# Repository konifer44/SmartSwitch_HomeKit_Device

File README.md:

# SmartSwitch compatible with Apple HomeKit Protocol

<br/>

# Project overview

The remotely operated SmartSwitch is designed to turn electrical devices or circuits on and off. The compact size of the device allows for the product to be installed in the housings of other devices. Thanks to its miniature size it fits most of the flush-mounted junction boxes and light switch sockets. The devices can be controlled either via the Apple HomeKit or with buttons connected directly to them.
Using Apple Home app enables automations, scenes and integration with Siri.

<br/>

# Electrical schematic
I have started with an electrical schematic of my device. The basic connections are as specified by the chip manufacturer in [ESP32-WROOM-32d-Datasheet] and the rest depends on my knowledge, experience, and prototyping. 
After creating a schematic I connected all elements on a breadboard. When the breadboard prototype worked successfully I attempted to make PCB.

## Hardware files (v4.0)

- [Eagle schematic (.sch)](hardware/v4.0/smart%20switch.sch)
- [Eagle PCB layout (.brd)](hardware/v4.0/smart%20switch.brd)

## Parts list

| Reference | Qty | Model / value | Function |
| --- | --- | --- | --- |
| U3 | 1 | ESP-WROOM-32 | Wi-Fi and HomeKit controller. |
| HLK1 | 1 | HLK-PM03, 3.3 V (README); HLK-PM01 library device in Eagle | AC-to-DC supply feeding the ESP32 3V3 rail. |
| U2 | 1 | SN74LVC2G17DBV (schematic) | Schmitt-trigger buffer for the physical-switch input to GPIO13. |
| K2 | 1 | OJE-SS-103HM,000 | Normally open load-switching relay. |
| Q1 | 1 | BC849 family, SOT-23 | Relay-coil driver controlled by GPIO27. |
| D1 (formerly R3) | 1 | Diode; model not specified | Coil flyback protection: cathode to VCC, anode to Q1 collector. |
| R1 | 1 | 10 kΩ, 1206 | Physical-switch input pull-down; forms an RC network with C5/C6. |
| R2 | 1 | 10 kΩ, 1206 | ESP32 EN pull-up; forms the reset RC network with C3. |
| R4 | 1 | 4.7 kΩ, 1206 | Q1 base-current limiting. |
| R5 | 1 | 10 kΩ, 1206 | Q1 base-to-emitter pull-down. |
| C1, C2 | 2 | Not specified, 1206 | Supply filtering between VCC and GND. |
| C3 | 1 | Not specified, 1206 | EN-to-GND capacitor in the reset RC network. |
| C4 | 1 | Not specified, polarized, E2-5 footprint | Supply reservoir capacitor between VCC and GND. |
| C5, C6 | 2 | Not specified; C5: C025-024X044, C6: 1206 | Parallel capacitors from switch input to VCC; input filtering with R1. |
| JP1 | 1 | 1×4 header | Programming: GND, RXD0, TXD0, VCC (3.3 V). |
| JP2 | 1 | 1×2 header | GPIO0-to-GND boot-mode jumper. |
| X1 | 1 | AK500/5 terminal block | AC supply, relay contacts, and physical-switch connections. |

The capacitors provide basic power-supply and input filtering, with C3 forming the ESP32 enable/reset RC network. For typical ESP32 supply-decoupling and EN/reset capacitor values, refer to Espressif’s basic ESP32 reference schematics.

<br/>

# PCB designing
The PCB design is based on my electrical schematic. The first step was creating a homemade PCB prototype. When the whole device was mounted, flashed, tested, and running finely I've ordered PCB from [ALLPCB] 

<br/>

## PCB design

<br/>

## Ordered PCB

<br/>

## Prototype & manufactured PCB

<br/><br/>

# Assembly
I have all needed tools and skills to build and flash my device at home .

<br/>

# Writing program 
When I started this project HomeKit Accessory Development Kit (ADK) was available only for MFi Program, also ESP32 manufacture didn't provide any information on how to establish HomeKit connection. I decided to use and modify code from: 
[maximkulkin/esp-homekit]

The whole communication is based on HomeKit Accessory Server from Maxim, but how physically device is working is all my job.
Because Apple doesn't allow to use Apple's WAC (Wireless Accessory Configuration) feature for devices without MFi license we need to provide WiFi credentials in another way.
In Maxim's project the WiFi Credentials are hardcoded and cannot be modified after flashing the device. I have added support for [ESP-IDF Wi-Fi Provisioning], now user can provide WiFi credentials via [ESP SoftAP Provisioning] app even after flashing accessory. The next feature I have added is support for two ways of controlling the accessory. First directly from HomeKit app and the second one by the current wall-mounted physical switch.

## Flashing

<br/>

# Final Mounting

>
* The device is designed to control other electrical devices and
operate in their housings. Faulty connection or use may result in fire or electric shock.

* All works on the device may be performed only by a qualified and licensed electrician. Observe national regulations.

* Even when the device is turned off, voltage may be present at
its terminals. Any maintenance introducing changes into the configuration of connections or the load must be always performed with the disabled fuse or power supply.

<br/>

<br/>

## Provisioning WiFi credentials & adding to HomeKit
As I mentioned before Apple doesn't allow to use Apple's WAC (Wireless Accessory Configuration) feature for devices without MFi license so we will use an official application which is available in AppStore: [ESP SoftAP Provisioning] from [ESP32] manufacturer. After successfully connecting to WiFi the HomeKit Accessory is ready to add to your home.

<br/><br/>

[ESP32]: <https://www.espressif.com/en/products/socs/esp32>
[ESP-IDF]: <https://docs.espressif.com/projects/esp-idf/en/latest/esp32/>
[ESP-IDF Wi-Fi Provisioning]: <https://docs.espressif.com/projects/esp-idf/en/latest/esp32/api-reference/provisioning/wifi_provisioning.html#>

[ESP SoftAP Provisioning]: <https://apps.apple.com/us/app/esp-softap-provisioning/id1474040630>
[LEDC documentation]: <https://docs.espressif.com/projects/esp-idf/en/latest/esp32/api-reference/peripherals/ledc.html>
[Bluetooth Example Walkthrough]: <https://github.com/espressif/esp-idf/blob/1067b28707e527f177752741e3aa08b5dc64a4d7/examples/bluetooth/bluedroid/ble/gatt_server_service_table/tutorial/Gatt_Server_Service_Table_Example_Walkthrough.md>

[ALLPCB]: <https://www.allpcb.com>
[maximkulkin/esp-homekit]: <https://github.com/maximkulkin/esp-homekit>
[ESP32-WROOM-32d-Datasheet]: <https://www.espressif.com/sites/default/files/documentation/esp32-wroom-32d_esp32-wroom-32u_datasheet_en.pdf>

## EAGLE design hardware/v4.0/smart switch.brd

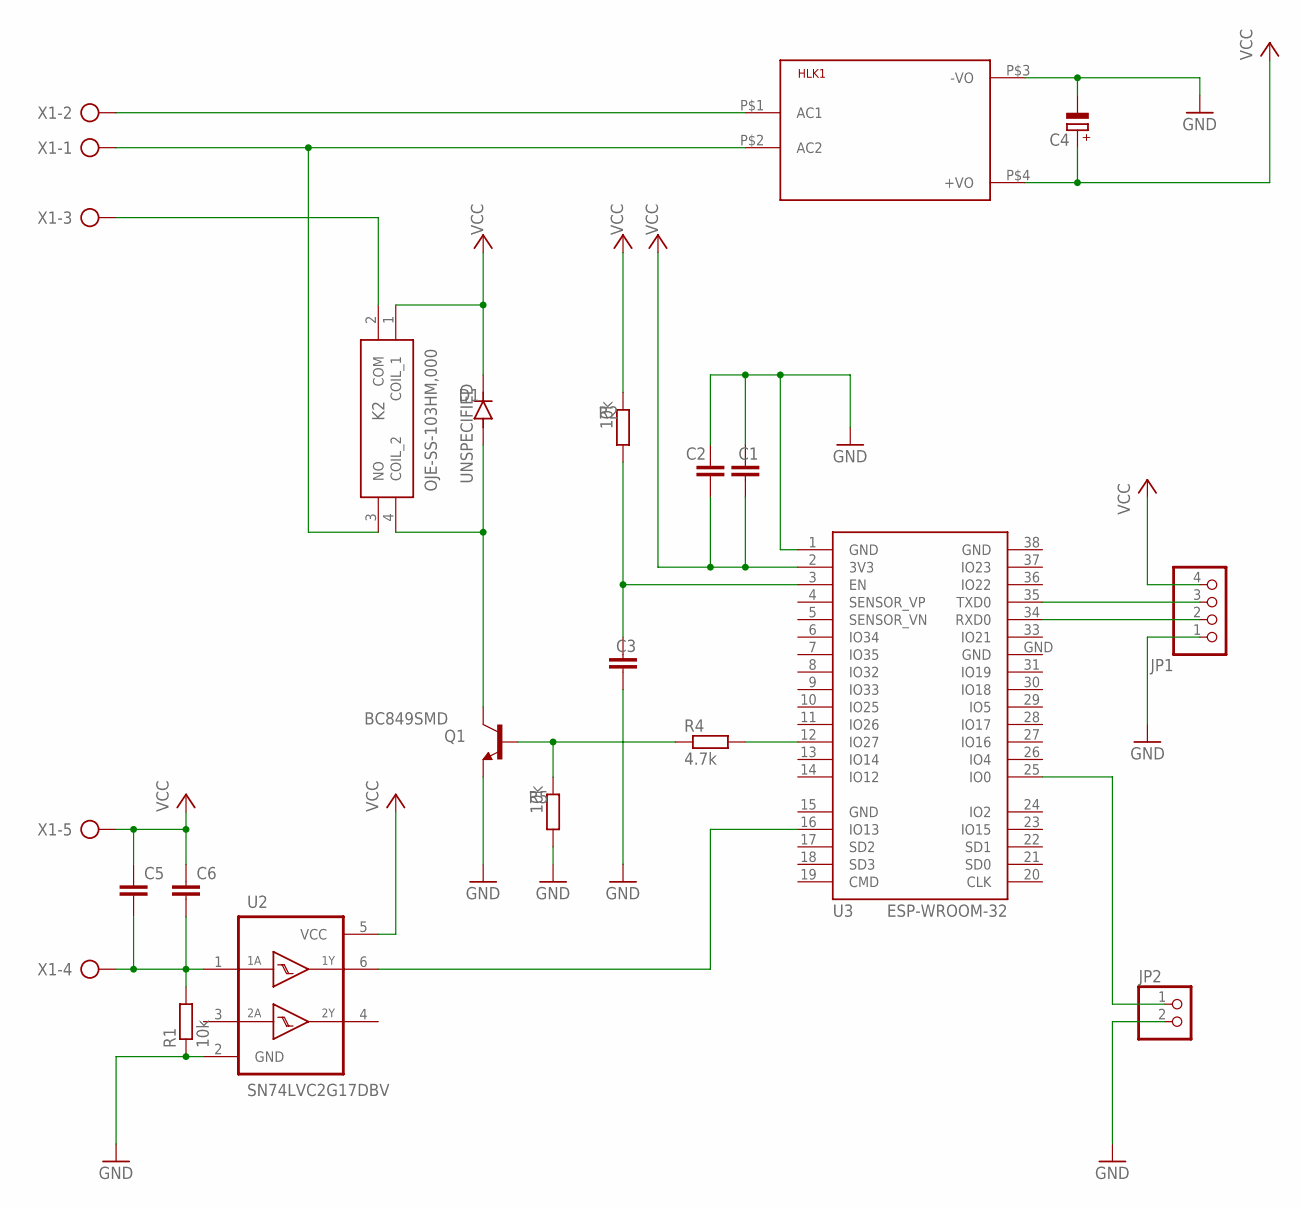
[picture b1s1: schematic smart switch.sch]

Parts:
C1, C2, C3, C6: C-EUC1206; C1206
C4: CPOL-EUE2-5; E2-5
C5: C-EU025-024X044; C025-024X044
D1: UNSPECIFIED; DIODE-LEGACY-R3
HLK1: HLK-PM013W; HLK-PM01
JP1: PINHD-1X4; 1X04
JP2: PINHD-1X2; 1X02
K2: OJE-SS-103HM,000; OJESS103HM000
Q1: BC849SMD; SOT23-BEC
R1, R2, R5: 10k; R1206
R4: 4.7k; R1206
U2: SN74LVC2G17DBV; SOT23-6
U3: ESP-WROOM-32
X1: AK500/5

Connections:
GND: C1.1, C2.1, C3.2, C4.-, HLK1.P$3 (-VO), JP1.1, JP2.2, Q1.E, R1.1, R5.2, U2.2 (GND), U3.1 (GND), U3.15 (GND), U3.38 (GND), U3.GND
unnamed: K2.2 (COM), X1.3
unnamed: D1.A, K2.4 (COIL_2), Q1.C
unnamed: JP1.3, U3.35 (TXD0)
unnamed: C5.2, C6.2, R1.2, U2.1 (1A), X1.4
unnamed: JP1.2, U3.34 (RXD0)
unnamed: JP2.1, U3.25 (IO0)
unnamed: R4.2, U3.12 (IO27)
unnamed: C3.1, R2.2, U3.3 (EN)
unnamed: U2.6 (1Y), U3.16 (IO13)
unnamed: HLK1.P$2 (AC2), K2.3 (NO), X1.1
unnamed: HLK1.P$1 (AC1), X1.2
unnamed: Q1.B, R4.1, R5.1
VCC: C1.2, C2.2, C4.+, C5.1, C6.1, D1.K, HLK1.P$4 (+VO), JP1.4, K2.1 (COIL_1), R2.1, U2.5 (VCC), U3.2 (3V3), X1.5

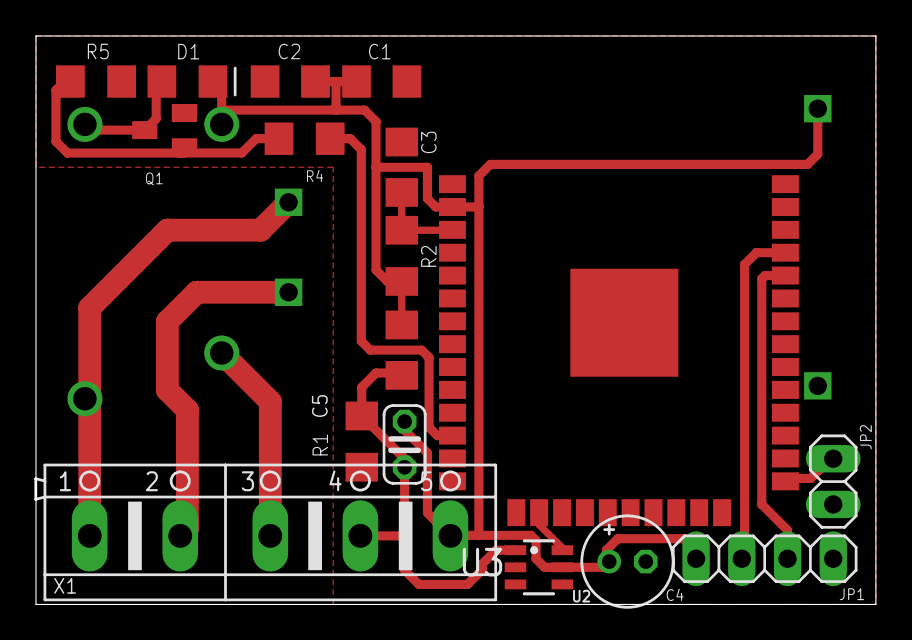
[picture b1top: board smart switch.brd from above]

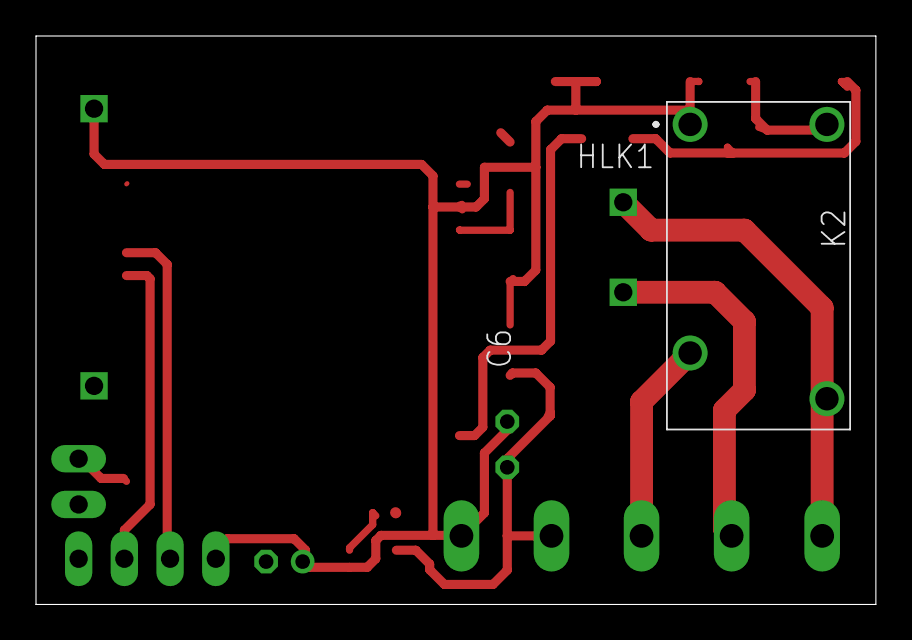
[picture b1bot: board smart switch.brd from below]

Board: 2 copper layers, 46.7 x 31.6 mm, 19 parts (2 on the bottom side), 14 nets.

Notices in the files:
parts and their libraries:
esp322: Creative Commons Attribution-ShareAlike 4.0 International
